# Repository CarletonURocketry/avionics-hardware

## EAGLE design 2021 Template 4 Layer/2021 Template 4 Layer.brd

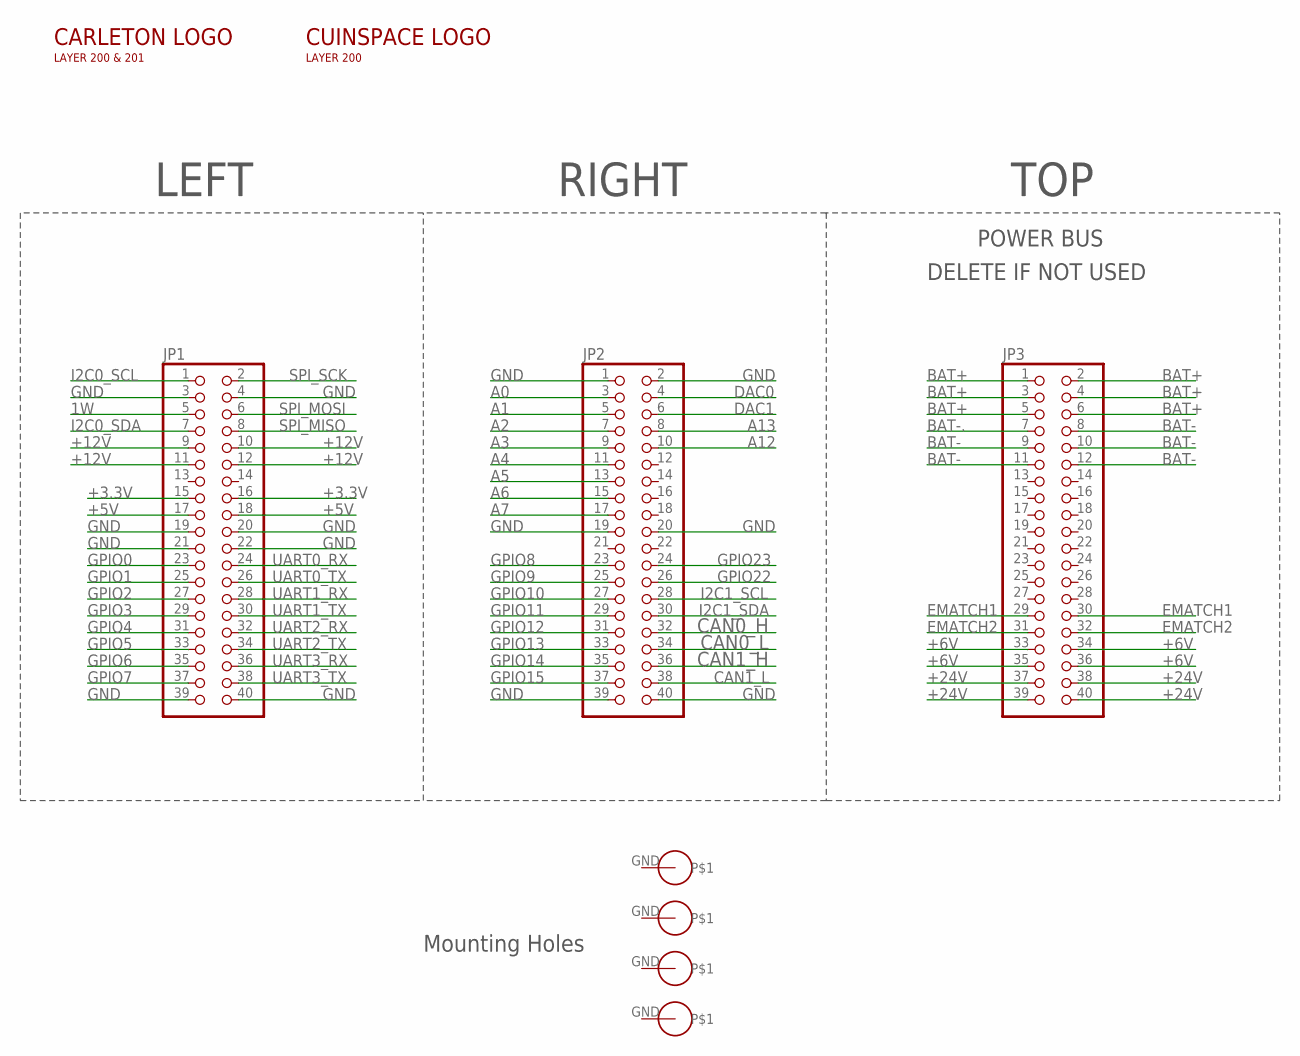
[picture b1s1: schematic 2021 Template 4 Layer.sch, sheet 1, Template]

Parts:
$$U$1: PS/104-MOUNTING-HOLE; PC/104-MOUNTING-HOLE
JP1, JP2, JP3: PINHD-2X20; 2X20
U$1, U$2, U$3: PS/104-MOUNTING-HOLE; PC/104-MOUNTING-HOLE
U$4: CARLETON3CM; CARLETONU_3CM
U$6: INSPACE3CM_L; INSPACE_3CM_LETTERS

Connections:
1W: JP1.5
+3.3V: JP1.15, JP1.16
+5V: JP1.17, JP1.18
+6V: JP3.33, JP3.34, JP3.35, JP3.36
+12V: JP1.9, JP1.10, JP1.11, JP1.12
+24V: JP3.37, JP3.38, JP3.39, JP3.40
A0: JP2.3
A1: JP2.5
A2: JP2.7
A3: JP2.9
A4: JP2.11
A5: JP2.13
A6: JP2.15
A7: JP2.17
A12: JP2.10
A13: JP2.8
BAT+: JP3.1, JP3.2, JP3.3, JP3.4, JP3.5, JP3.6
BAT-: JP3.8, JP3.9, JP3.10, JP3.11, JP3.12
BAT-.: JP3.7
CAN0_H: JP2.32
CAN0_L: JP2.34
CAN1_H: JP2.36
CAN1_L: JP2.38
DAC0: JP2.4
DAC1: JP2.6
EMATCH1: JP3.29, JP3.30
EMATCH2: JP3.31, JP3.32
GND: JP1.3, JP1.4, JP1.19, JP1.20, JP1.21, JP1.22, JP1.39, JP1.40, JP2.1, JP2.2, JP2.19, JP2.20, JP2.39, JP2.40
GPIO0: JP1.23
GPIO1: JP1.25
GPIO2: JP1.27
GPIO3: JP1.29
GPIO4: JP1.31
GPIO5: JP1.33
GPIO6: JP1.35
GPIO7: JP1.37
GPIO8: JP2.23
GPIO9: JP2.25
GPIO10: JP2.27
GPIO11: JP2.29
GPIO12: JP2.31
GPIO13: JP2.33
GPIO14: JP2.35
GPIO15: JP2.37
GPIO22: JP2.26
GPIO23: JP2.24
I2C0_SCL: JP1.1
I2C0_SDA: JP1.7
I2C1_SCL: JP2.28
I2C1_SDA: JP2.30
SPI_MISO: JP1.8
SPI_MOSI: JP1.6
SPI_SCK: JP1.2
UART0_RX: JP1.24
UART0_TX: JP1.26
UART1_RX: JP1.28
UART1_TX: JP1.30
UART2_RX: JP1.32
UART2_TX: JP1.34
UART3_RX: JP1.36
UART3_TX: JP1.38

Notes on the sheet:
POWER BUS
DELETE IF NOT USED
LEFT
RIGHT
TOP
Mounting Holes

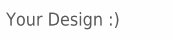
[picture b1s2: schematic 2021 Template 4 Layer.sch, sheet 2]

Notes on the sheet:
Your Design :)

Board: 4 copper layers, 9 parts (0 on the bottom side), 10 nets, no tracks yet.

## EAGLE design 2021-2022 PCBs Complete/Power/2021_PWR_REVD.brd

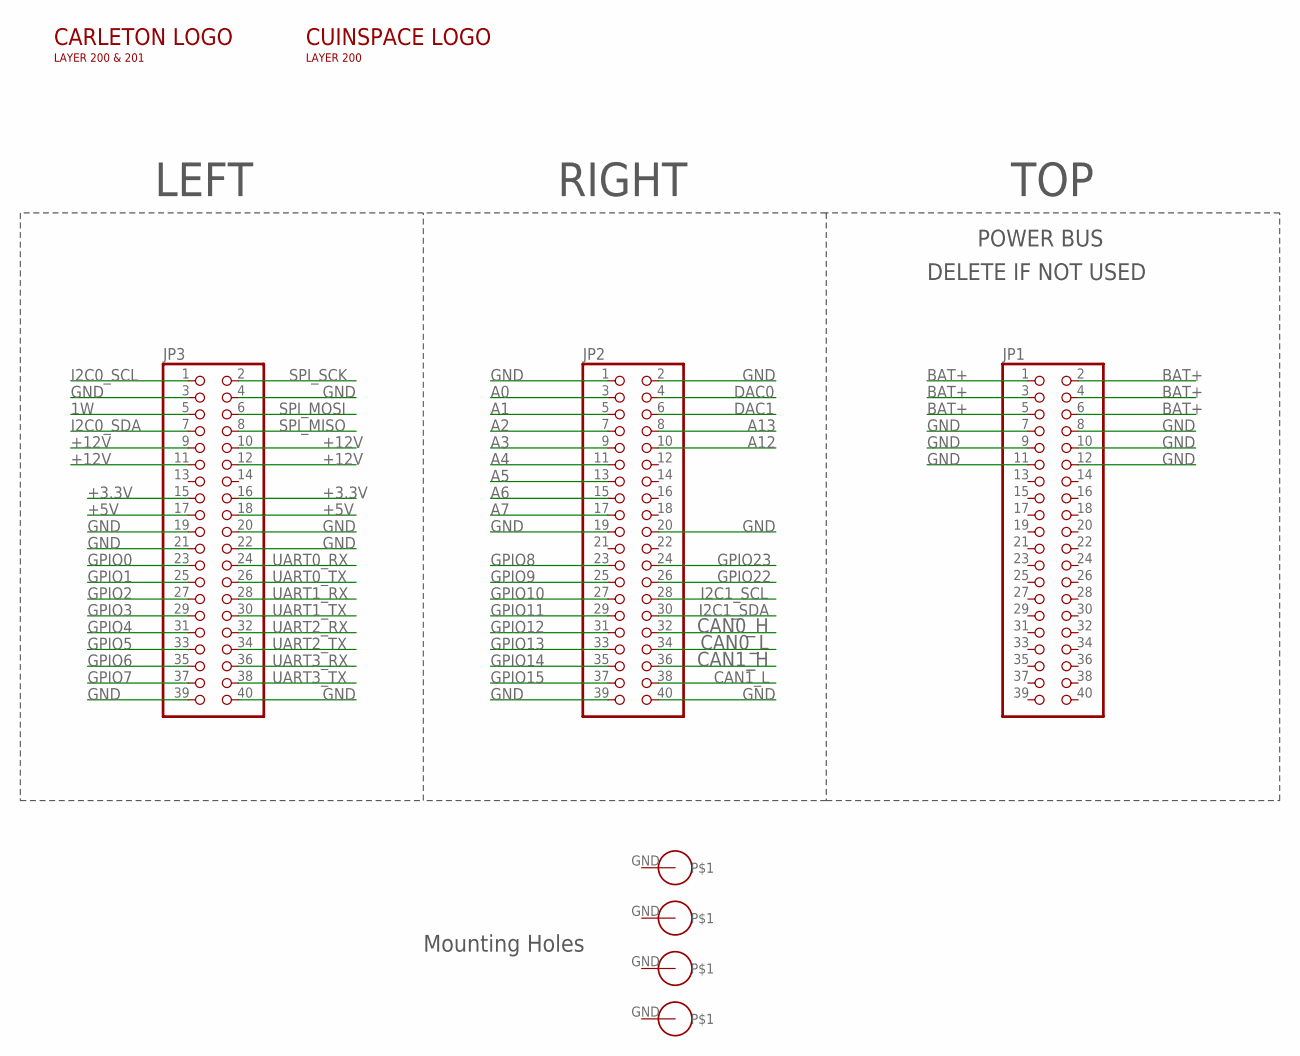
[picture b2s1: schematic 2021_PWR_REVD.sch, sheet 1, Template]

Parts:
$$U$1: PS/104-MOUNTING-HOLE; PC/104-MOUNTING-HOLE
JP1, JP2, JP3: PINHD-2X20; 2X20
U$1, U$2, U$3: PS/104-MOUNTING-HOLE; PC/104-MOUNTING-HOLE
U$100: INSPACE3CM_L; INSPACE_3CM_LETTERS
U$101: CARLETON3CM; CARLETONU_3CM

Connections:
1W: JP3.5
+3.3V: JP3.15, JP3.16; also elsewhere on the board
+5V: JP3.17, JP3.18; also elsewhere on the board
+12V: JP3.9, JP3.10, JP3.11, JP3.12; also elsewhere on the board
A0: JP2.3; also elsewhere on the board
A1: JP2.5; also elsewhere on the board
A2: JP2.7; also elsewhere on the board
A3: JP2.9
A4: JP2.11
A5: JP2.13
A6: JP2.15
A7: JP2.17
A12: JP2.10
A13: JP2.8
BAT+: JP1.1, JP1.2, JP1.3, JP1.4, JP1.5, JP1.6; also elsewhere on the board
CAN0_H: JP2.32
CAN0_L: JP2.34
CAN1_H: JP2.36
CAN1_L: JP2.38
DAC0: JP2.4
DAC1: JP2.6
GND: JP1.7, JP1.8, JP1.9, JP1.10, JP1.11, JP1.12, JP2.1, JP2.2, JP2.19, JP2.20, JP2.39, JP2.40, JP3.3, JP3.4, JP3.19, JP3.20, JP3.21, JP3.22, JP3.39, JP3.40; also elsewhere on the board
GPIO0: JP3.23
GPIO1: JP3.25
GPIO2: JP3.27
GPIO3: JP3.29
GPIO4: JP3.31
GPIO5: JP3.33
GPIO6: JP3.35
GPIO7: JP3.37
GPIO8: JP2.23
GPIO9: JP2.25
GPIO10: JP2.27
GPIO11: JP2.29
GPIO12: JP2.31; also elsewhere on the board
GPIO13: JP2.33
GPIO14: JP2.35
GPIO15: JP2.37
GPIO22: JP2.26
GPIO23: JP2.24
I2C0_SCL: JP3.1
I2C0_SDA: JP3.7
I2C1_SCL: JP2.28
I2C1_SDA: JP2.30
SPI_MISO: JP3.8
SPI_MOSI: JP3.6
SPI_SCK: JP3.2
UART0_RX: JP3.24
UART0_TX: JP3.26
UART1_RX: JP3.28
UART1_TX: JP3.30
UART2_RX: JP3.32
UART2_TX: JP3.34
UART3_RX: JP3.36
UART3_TX: JP3.38

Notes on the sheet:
POWER BUS
DELETE IF NOT USED
LEFT
RIGHT
TOP
Mounting Holes

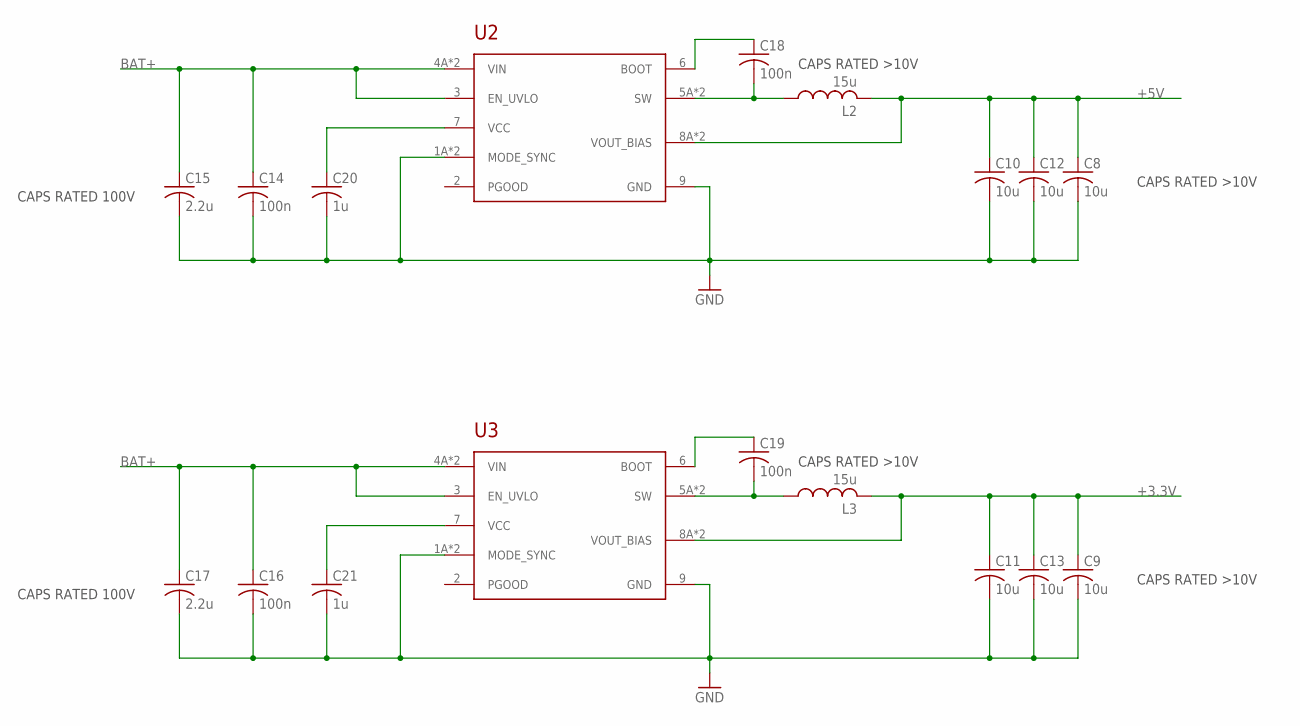
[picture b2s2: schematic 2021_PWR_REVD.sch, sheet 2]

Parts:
C8, C9, C10, C11, C12, C13: 10u; C0805
C14, C16, C18, C19: 100n; C0805
C15, C17: 2.2u; C0805
C20, C21: 1u; C0805
L2, L3: 15u; 13.5X12.5
U2, U3: LMR36506LMR36506MSC3; 9-VFQFN

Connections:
+3.3V: C9.1, C11.1, C13.1, L3.P$2 (2), U3.8A (VOUT_BIAS), U3.8B (VOUT_BIAS); also elsewhere on the board
+5V: C8.1, C10.1, C12.1, L2.P$2 (2), U2.8A (VOUT_BIAS), U2.8B (VOUT_BIAS); also elsewhere on the board
BAT+: C14.1, C15.1, C16.1, C17.1, U2.3 (EN_UVLO), U2.4A (VIN), U2.4B (VIN), U3.3 (EN_UVLO), U3.4A (VIN), U3.4B (VIN); also elsewhere on the board
GND: C8.2, C9.2, C10.2, C11.2, C12.2, C13.2, C14.2, C15.2, C16.2, C17.2, C20.2, C21.2, U2.1A (MODE_SYNC), U2.1B (MODE_SYNC), U2.9 (GND), U3.1A (MODE_SYNC), U3.1B (MODE_SYNC), U3.9 (GND); also elsewhere on the board
unnamed: C18.1, U2.6 (BOOT)
unnamed: C18.2, L2.P$1 (1), U2.5A (SW), U2.5B (SW)
unnamed: C20.1, U2.7 (VCC)
unnamed: C19.1, U3.6 (BOOT)
unnamed: C19.2, L3.P$1 (1), U3.5A (SW), U3.5B (SW)
unnamed: C21.1, U3.7 (VCC)

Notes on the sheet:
CAPS RATED >10V
CAPS RATED 100V

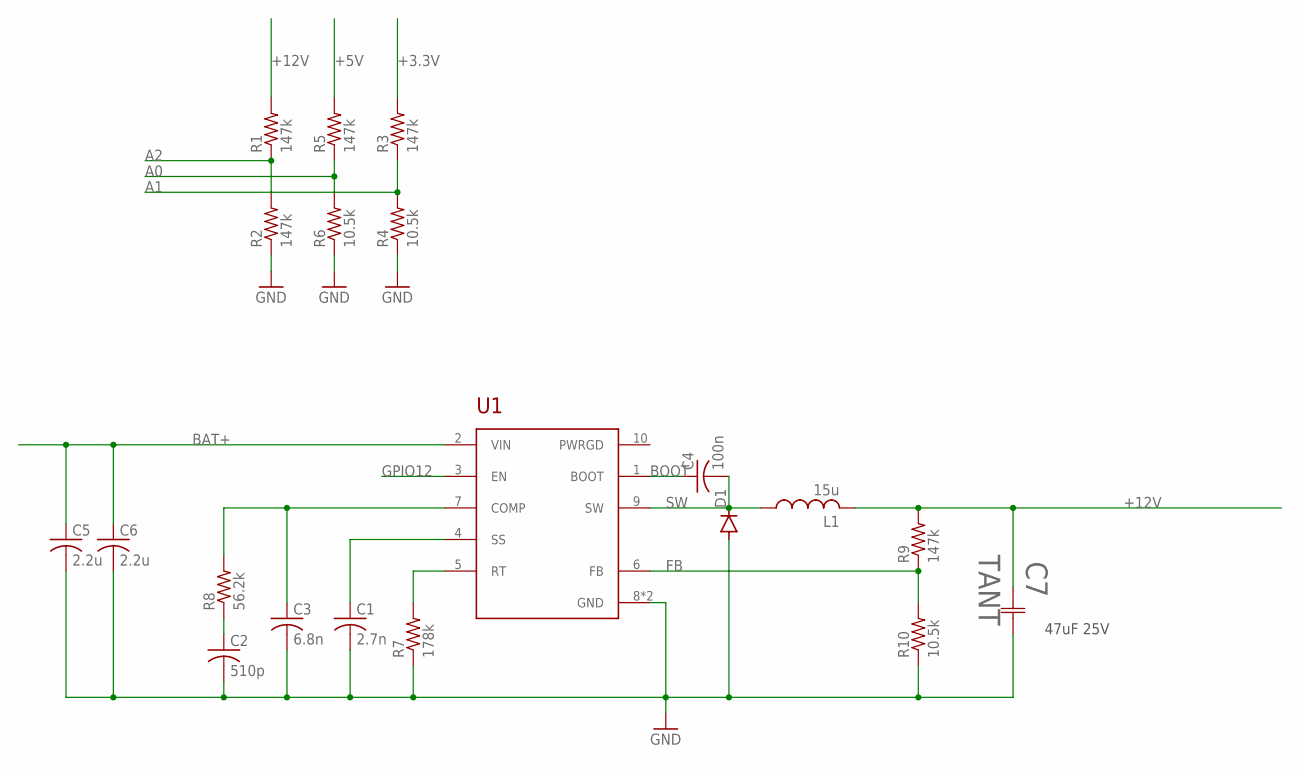
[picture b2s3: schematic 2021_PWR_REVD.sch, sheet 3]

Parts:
C1: 2.7n; C0805
C2: 510p; C0805
C3: 6.8n; C0805
C4: 100n; C0805
C5, C6: 2.2u; C0805
C7: TANT; TAJD
D1: SCH_DIODE_10A_100VFSV10100V; TO-277-3
L1: 15u; 13.5X12.5
R1, R2, R3, R5, R9: 147k; R0805
R4, R6, R10: 10.5k; R0805
R7: 178k; R0805
R8: 56.2k; R0805
U1: TPS54561; 10-WSON

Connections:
+3.3V: R3.2; also elsewhere on the board
+5V: R5.2; also elsewhere on the board
+12V: C7.1 (11), L1.P$2 (2), R1.2, R9.2; also elsewhere on the board
A0: R5.1, R6.2; also elsewhere on the board
A1: R3.1, R4.2; also elsewhere on the board
A2: R1.1, R2.2; also elsewhere on the board
BAT+: C5.1, C6.1, U1.2 (VIN); also elsewhere on the board
BOOT: C4.1, U1.1 (BOOT)
FB: R9.1, R10.2, U1.6 (FB)
GND: C1.2, C2.2, C3.2, C5.2, C6.2, C7.2 (22), D1.P$2 (A), D1.P$3 (A), R2.1, R4.1, R6.1, R7.1, R10.1, U1.8 (GND), U1.11 (GND); also elsewhere on the board
GPIO12: U1.3 (EN); also elsewhere on the board
unnamed: R7.2, U1.5 (RT)
unnamed: C2.1, R8.1
unnamed: C3.1, R8.2, U1.7 (COMP)
unnamed: C1.1, U1.4 (SS)
SW: C4.2, D1.P$1 (C), L1.P$1 (1), U1.9 (SW)

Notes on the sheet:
47uF 25V

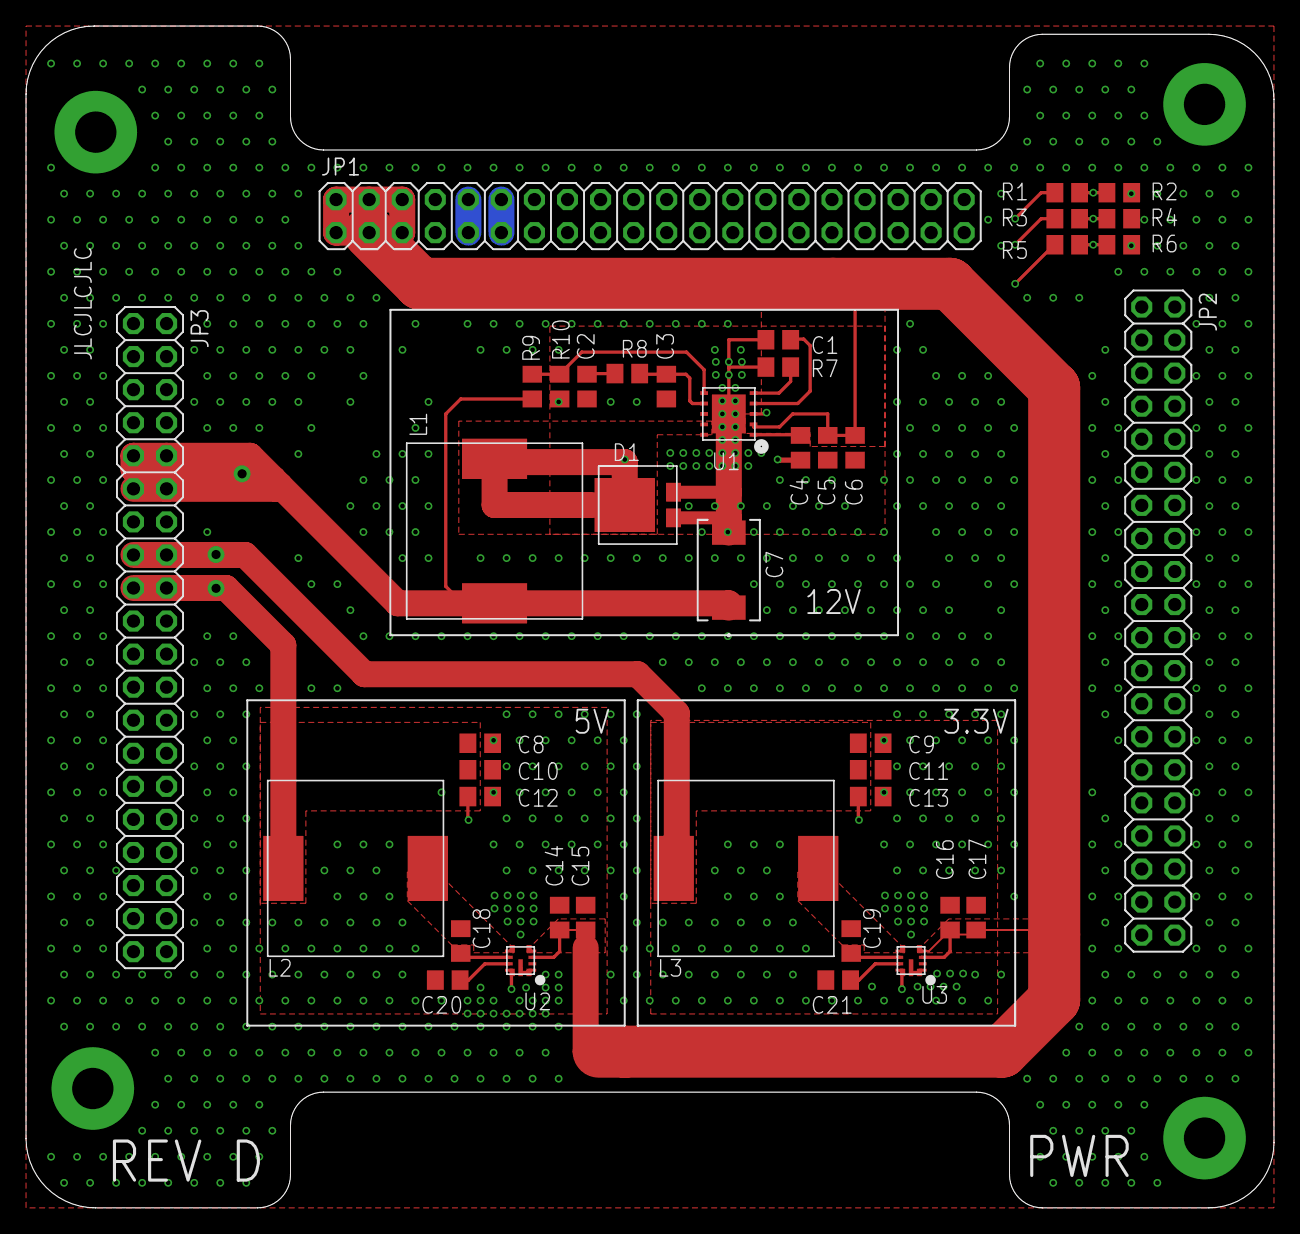
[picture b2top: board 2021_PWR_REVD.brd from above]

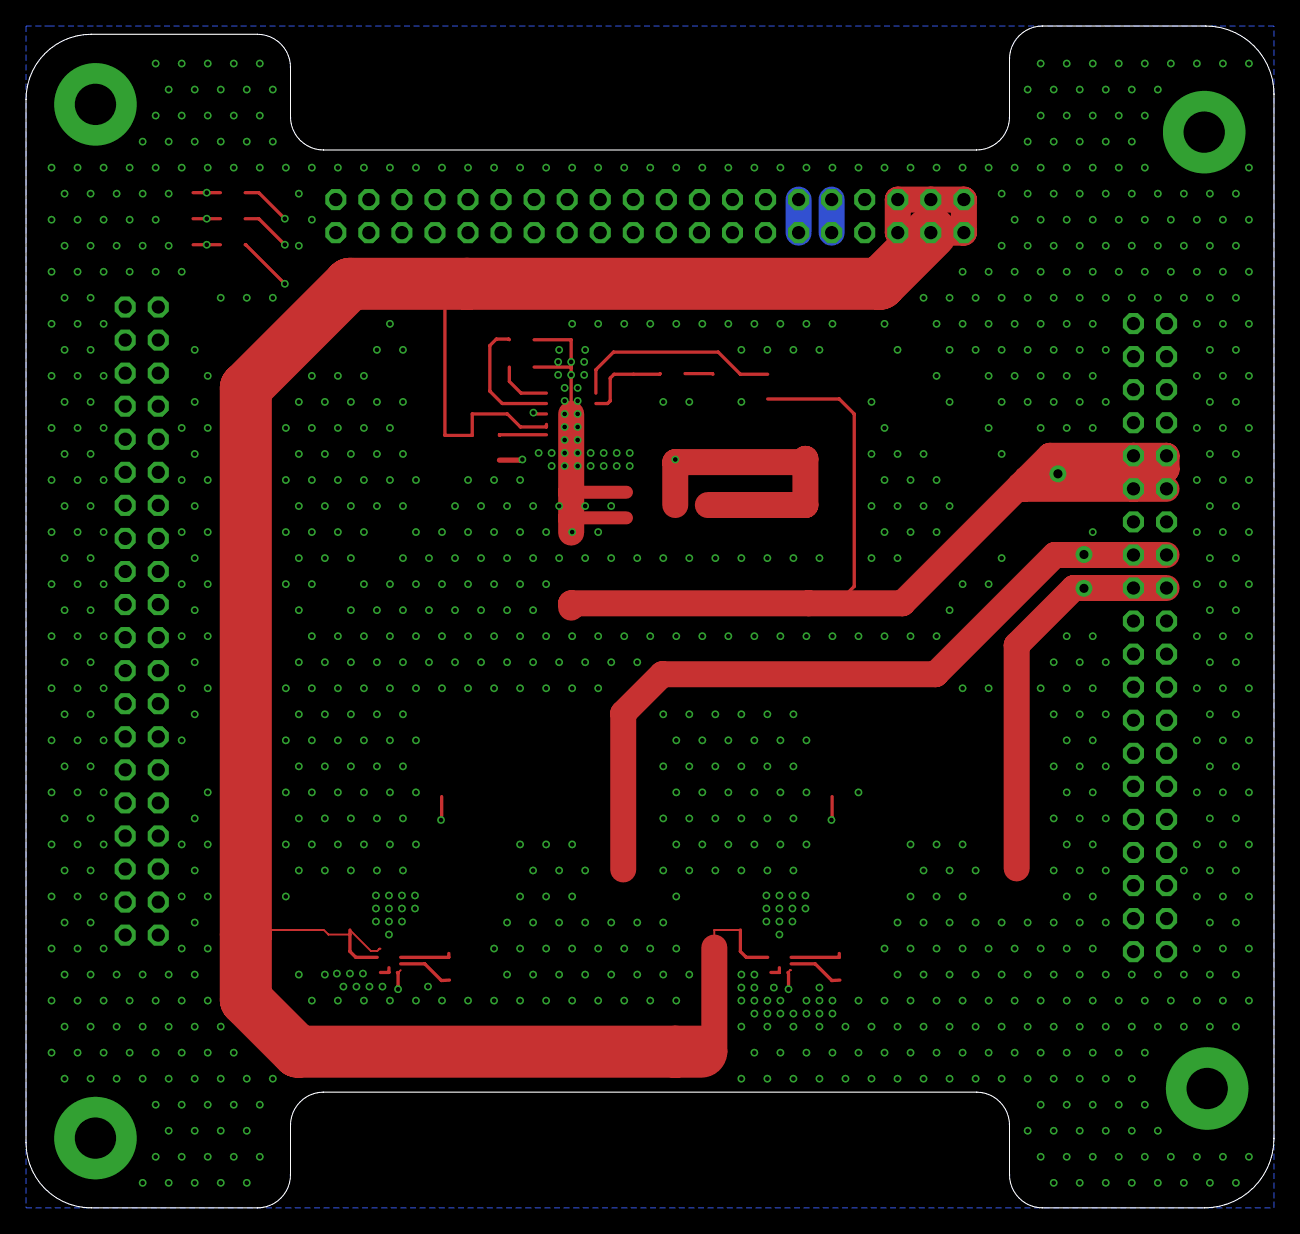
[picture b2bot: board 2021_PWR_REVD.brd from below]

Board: 4 copper layers, 95.9 x 90.8 mm, 47 parts (2 on the bottom side), 22 nets.

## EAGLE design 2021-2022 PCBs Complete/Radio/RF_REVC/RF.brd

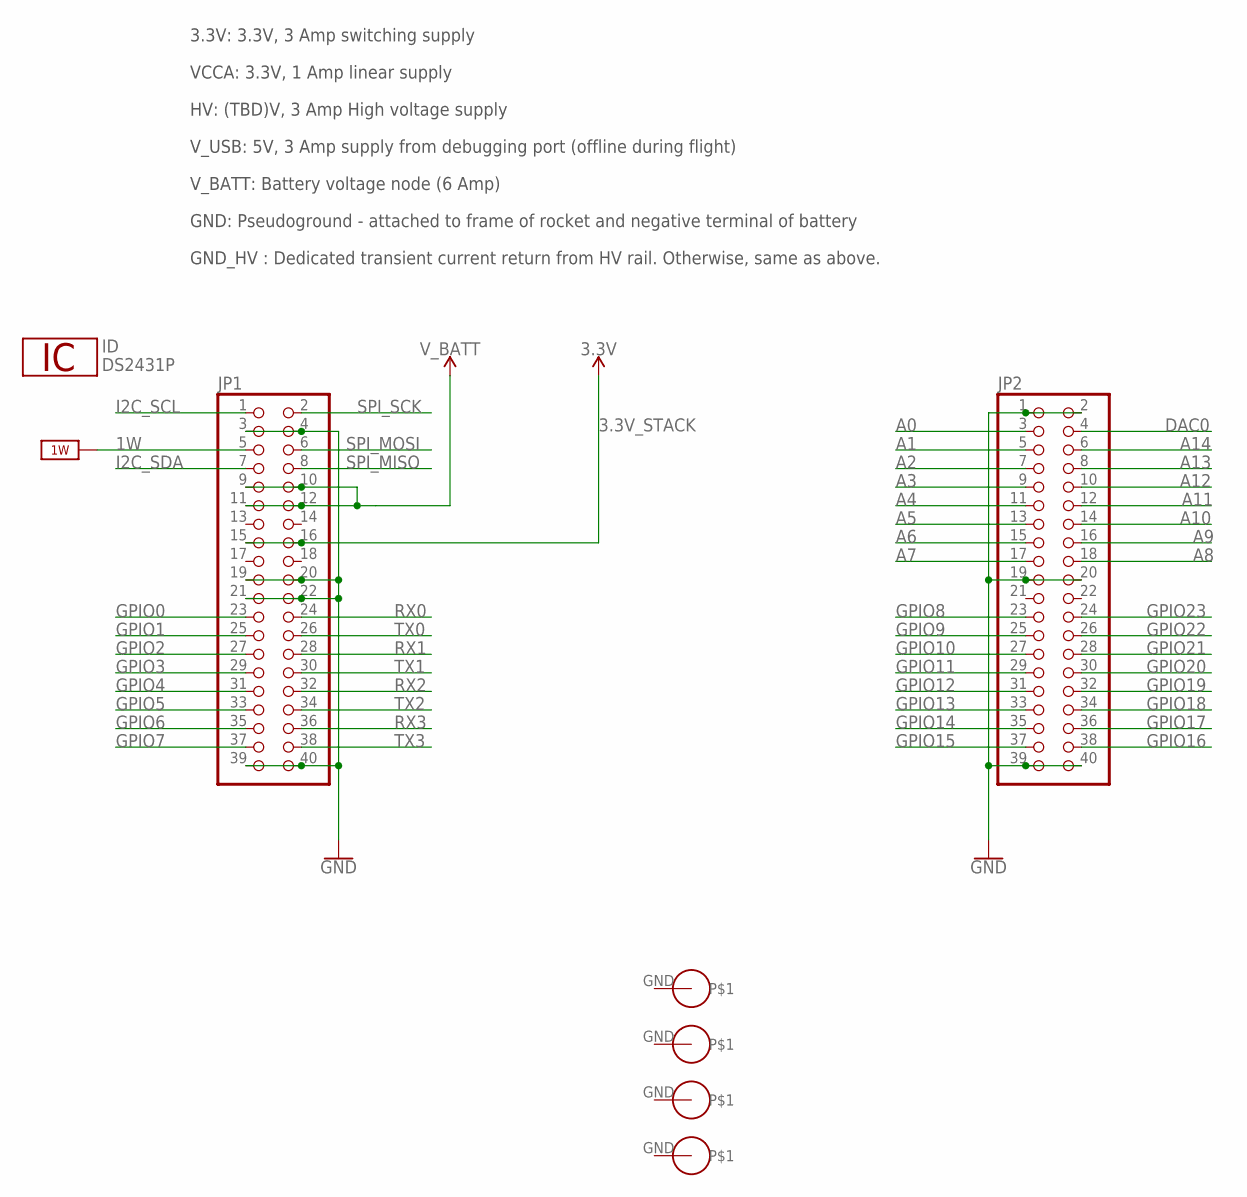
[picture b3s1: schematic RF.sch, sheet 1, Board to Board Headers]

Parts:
ID: DS2431P; TSOC6
JP1, JP2: PINHD-2X20; 2X20
U$1, U$2, U$3, U$4: PS/104-MOUNTING-HOLE; PC/104-MOUNTING-HOLE

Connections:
1W: ID.2 (1W), JP1.5
3.3V_STACK: JP1.15, JP1.16; also elsewhere on the board
A0: JP2.3
A1: JP2.5
A2: JP2.7
A3: JP2.9
A4: JP2.11
A5: JP2.13
A6: JP2.15
A7: JP2.17
A8: JP2.18
A9: JP2.16
A10: JP2.14
A11: JP2.12
A12: JP2.10
A13: JP2.8
A14: JP2.6
DAC0: JP2.4
GND: ID.1 (GND), JP1.3, JP1.4, JP1.19, JP1.20, JP1.21, JP1.22, JP1.39, JP1.40, JP2.1, JP2.2, JP2.19, JP2.20, JP2.39, JP2.40; also elsewhere on the board
GPIO0: JP1.23
GPIO1: JP1.25
GPIO2: JP1.27
GPIO3: JP1.29
GPIO4: JP1.31
GPIO5: JP1.33
GPIO6: JP1.35
GPIO7: JP1.37
GPIO8: JP2.23
GPIO9: JP2.25
GPIO10: JP2.27
GPIO11: JP2.29
GPIO12: JP2.31
GPIO13: JP2.33
GPIO14: JP2.35
GPIO15: JP2.37
GPIO16: JP2.38
GPIO17: JP2.36
GPIO18: JP2.34
GPIO19: JP2.32
GPIO20: JP2.30
GPIO21: JP2.28
GPIO22: JP2.26
GPIO23: JP2.24
I2C_SCL: JP1.1
I2C_SDA: JP1.7
unnamed: JP1.9, JP1.10, JP1.11, JP1.12
RX0: JP1.24; also elsewhere on the board
RX1: JP1.28; also elsewhere on the board
RX2: JP1.32; also elsewhere on the board
RX3: JP1.36
SPI_MISO: JP1.8
SPI_MOSI: JP1.6
SPI_SCK: JP1.2
TX0: JP1.26; also elsewhere on the board
TX1: JP1.30; also elsewhere on the board
TX2: JP1.34; also elsewhere on the board
TX3: JP1.38

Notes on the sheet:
VCCA: 3.3V, 1 Amp linear supply
HV: (TBD)V, 3 Amp High voltage supply
V_USB: 5V, 3 Amp supply from debugging port (offline during flight)
V_BATT: Battery voltage node (6 Amp)
3.3V: 3.3V, 3 Amp switching supply
GND: Pseudoground - attached to frame of rocket and negative terminal of battery
GND_HV : Dedicated transient current return from HV rail. Otherwise, same as above.

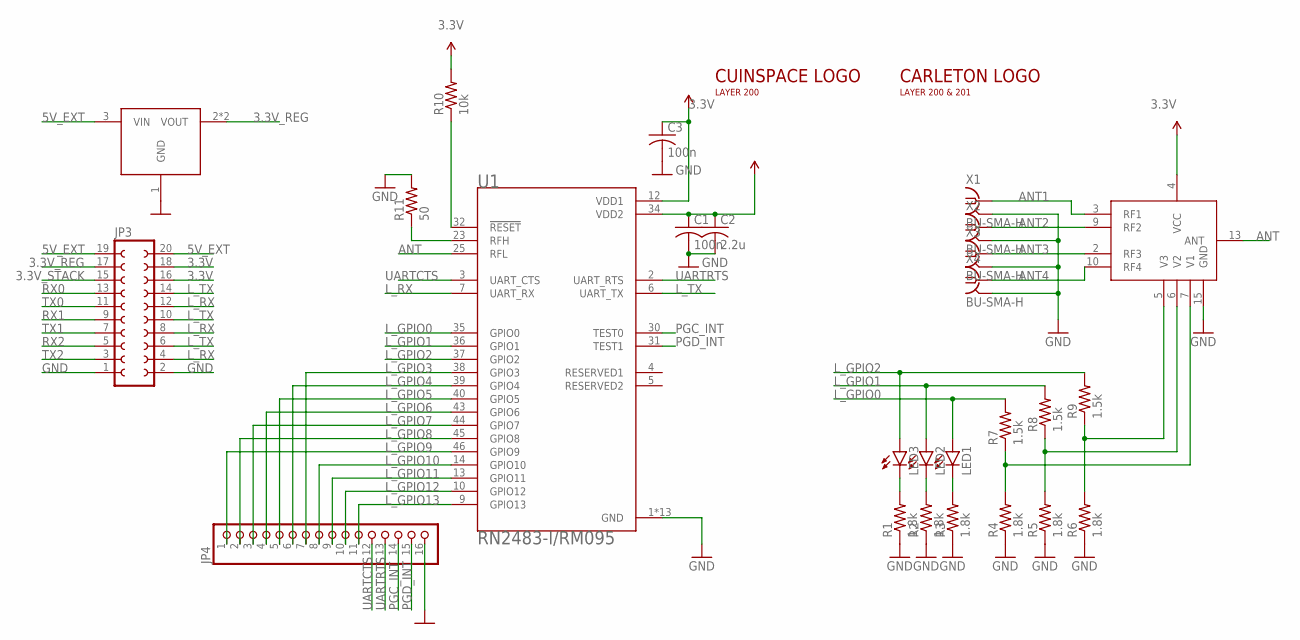
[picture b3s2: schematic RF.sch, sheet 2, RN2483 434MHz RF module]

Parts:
C1, C3: 100n; C0805
C2: 2.2u; C0805
JP3: FE10-2
JP4: PINHD-1X16; 1X16
LED1, LED2, LED3: LEDSMT1206; 1206
R1, R2, R3, R4, R5, R6: 1.8k; R0805
R7, R8, R9: 1.5k; R0805
R10: 10k; R0805
R11: 50; R0805
U1: RN2483-I/RM095; MICROCHIP_RN2483-I/RM095
U2: SKY13414; QFN45P200X200X55-15N
U3: LDL1117S33R; SOT223
U$6: INSPACE5CM_L; INSPACE_5CM_LETTERS
U$7: CARLETON3CM; CARLETONU_3CM
X1, X2, X3, X4: BU-SMA-H

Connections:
3.3V: C1.1, C2.1, C3.1, JP3.16, JP3.18, R10.2, U1.12 (VDD1), U1.34 (VDD2), U2.4 (VCC)
3.3V_REG: JP3.17, U3.2 (VOUT), U3.4 (VOUT)
3.3V_STACK: JP3.15; also elsewhere on the board
5V_EXT: JP3.19, JP3.20, U3.3 (VIN)
ANT: U1.25 (RFL), U2.13 (ANT)
ANT1: U2.3 (RF1), X1.1
ANT2: U2.9 (RF2), X2.1
ANT3: U2.2 (RF3), X3.1
ANT4: U2.10 (RF4), X4.1
GND: C1.2, C2.2, C3.2, JP3.1, JP3.2, JP4.16, R1.1, R2.1, R3.1, R4.1, R5.1, R6.1, R11.2, U1.1 (GND), U1.8 (GND), U1.11 (GND), U1.20 (GND), U1.21 (GND), U1.22 (GND), U1.24 (GND), U1.26 (GND), U1.27 (GND), U1.28 (GND), U1.33 (GND), U1.41 (GND), U1.47 (GND), U2.15 (GND), U3.1 (GND), X1.2, X1.3 (2), X1.4 (2), X1.5 (2), X2.2, X2.3 (2), X2.4 (2), X2.5 (2), X3.2, X3.3 (2), X3.4 (2), X3.5 (2), X4.2, X4.3 (2), X4.4 (2), X4.5 (2); also elsewhere on the board
L_GPIO0: LED1.A, R7.2, U1.35 (GPIO0)
L_GPIO1: LED2.A, R8.2, U1.36 (GPIO1)
L_GPIO2: LED3.A, R9.2, U1.37 (GPIO2)
L_GPIO3: JP4.7, U1.38 (GPIO3)
L_GPIO4: JP4.6, U1.39 (GPIO4)
L_GPIO5: JP4.5, U1.40 (GPIO5)
L_GPIO6: JP4.4, U1.43 (GPIO6)
L_GPIO7: JP4.3, U1.44 (GPIO7)
L_GPIO8: JP4.2, U1.45 (GPIO8)
L_GPIO9: JP4.1, U1.46 (GPIO9)
L_GPIO10: JP4.8, U1.14 (GPIO10)
L_GPIO11: JP4.9, U1.13 (GPIO11)
L_GPIO12: JP4.10, U1.10 (GPIO12)
L_GPIO13: JP4.11, U1.9 (GPIO13)
L_RX: JP3.4, JP3.8, JP3.12, U1.7 (UART_RX)
L_TX: JP3.6, JP3.10, JP3.14, U1.6 (UART_TX)
unnamed: R4.2, R7.1, U2.7 (V1)
unnamed: R5.2, R8.1, U2.6 (V2)
unnamed: R11.1, U1.23 (RFH)
unnamed: LED3.C, R1.2
unnamed: LED2.C, R2.2
unnamed: R6.2, R9.1, U2.5 (V3)
unnamed: R10.1, U1.32 (!RESET)
unnamed: LED1.C, R3.2
PGC_INT: JP4.14, U1.30 (TEST0)
PGD_INT: JP4.15, U1.31 (TEST1)
RX0: JP3.13; also elsewhere on the board
RX1: JP3.9; also elsewhere on the board
RX2: JP3.5; also elsewhere on the board
TX0: JP3.11; also elsewhere on the board
TX1: JP3.7; also elsewhere on the board
TX2: JP3.3; also elsewhere on the board
UARTCTS: JP4.12, U1.3 (UART_CTS)
UARTRTS: JP4.13, U1.2 (UART_RTS)

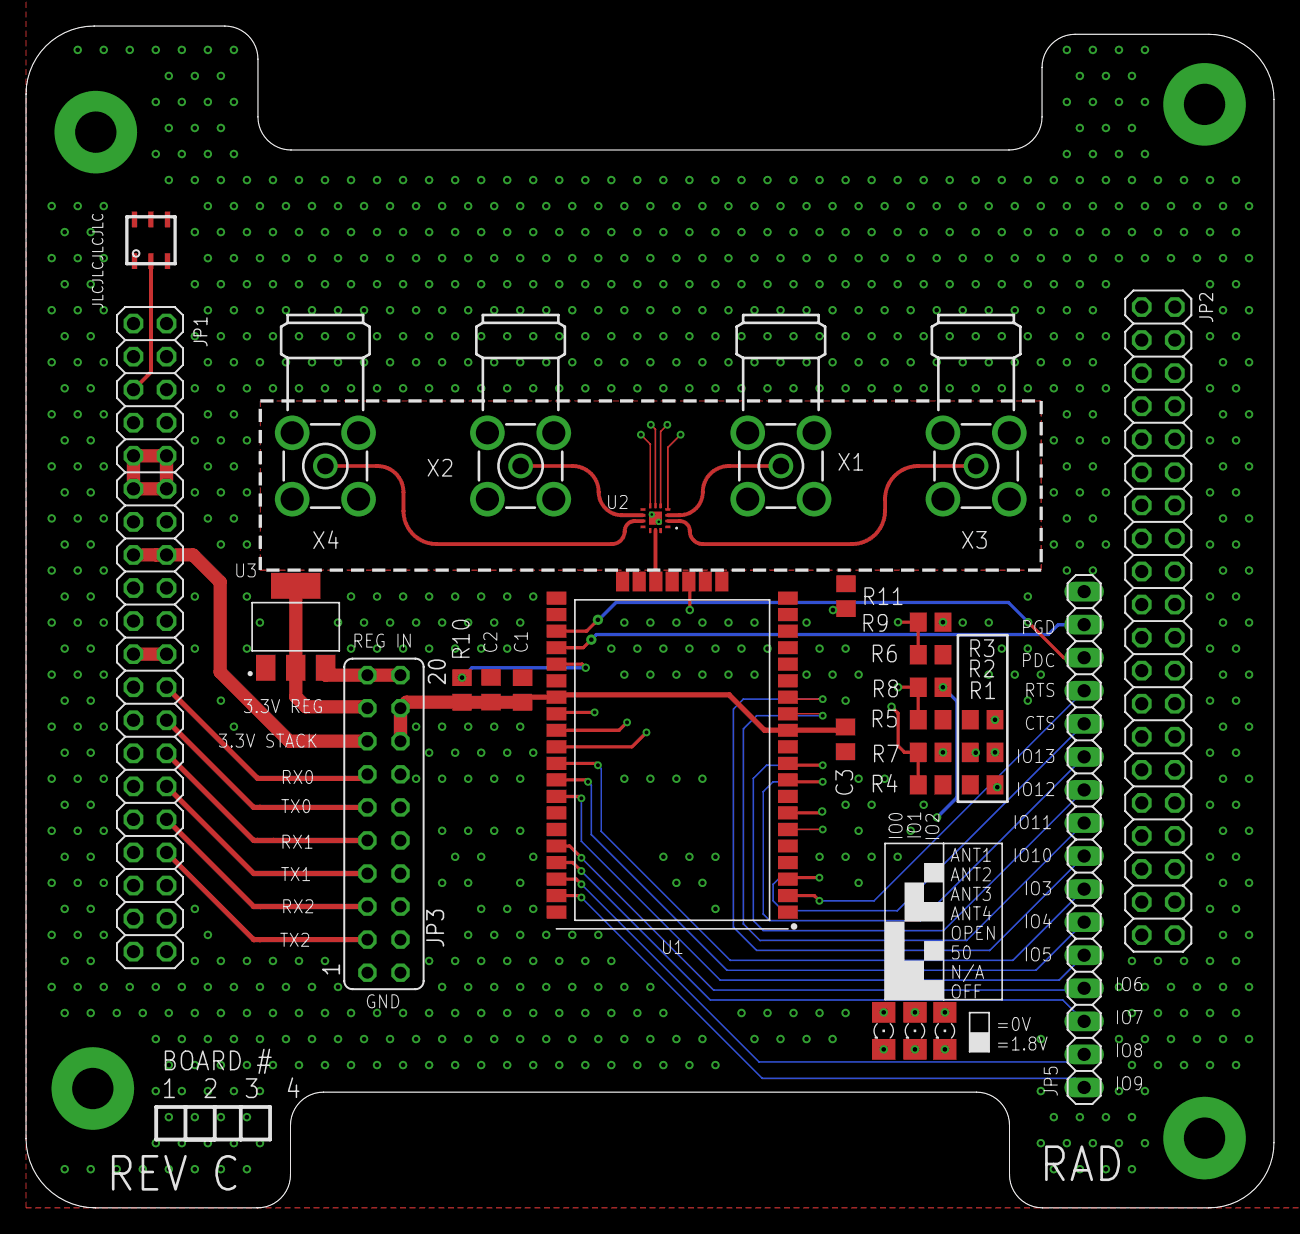
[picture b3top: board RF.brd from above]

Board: 4 copper layers, 95.9 x 90.8 mm, 35 parts (0 on the bottom side), 46 nets.

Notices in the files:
parts and their libraries:
SparkFun-PowerSymbols: Licensing: Creative Commons ShareAlike 4.0 International - https://creativecommons.org/licenses/by-sa/4.0
